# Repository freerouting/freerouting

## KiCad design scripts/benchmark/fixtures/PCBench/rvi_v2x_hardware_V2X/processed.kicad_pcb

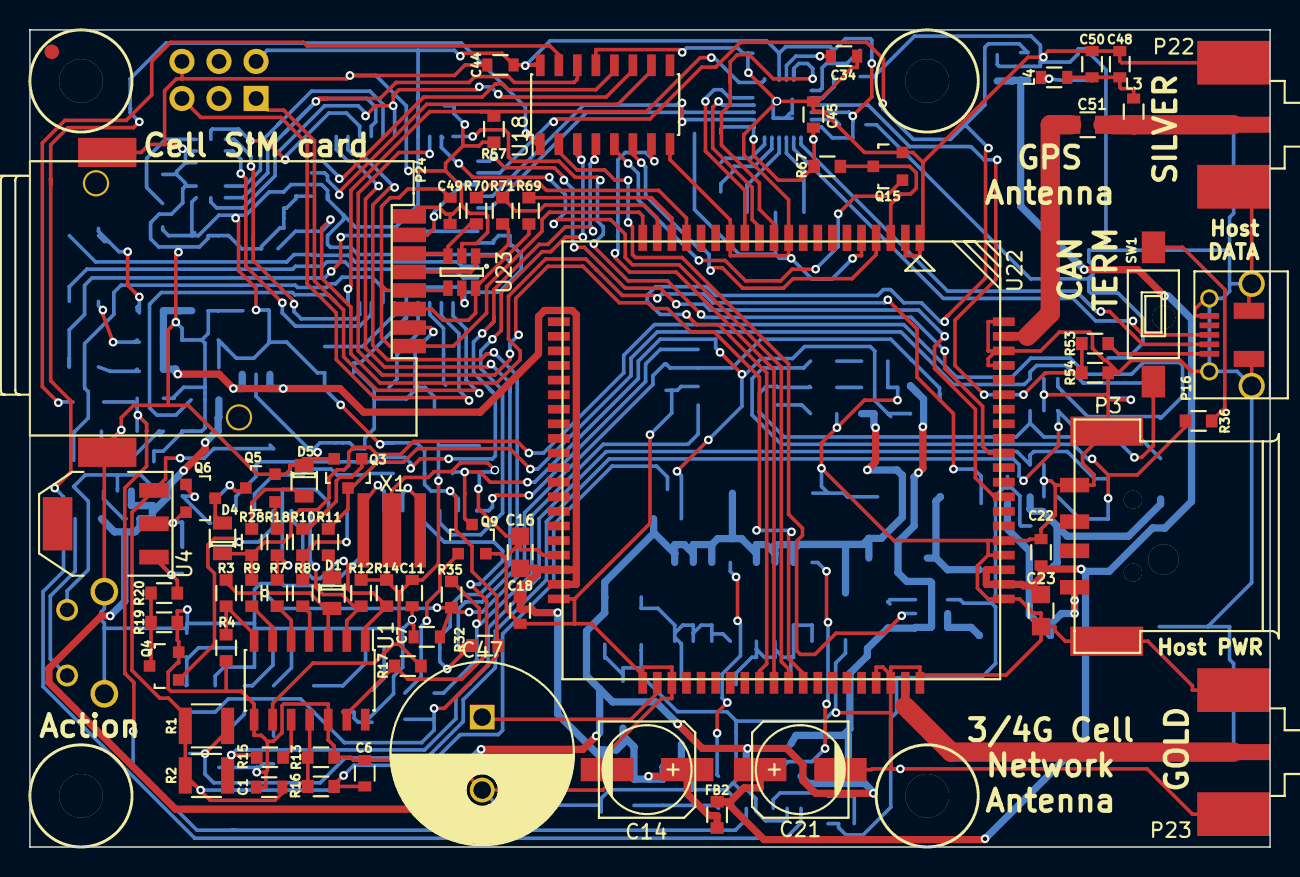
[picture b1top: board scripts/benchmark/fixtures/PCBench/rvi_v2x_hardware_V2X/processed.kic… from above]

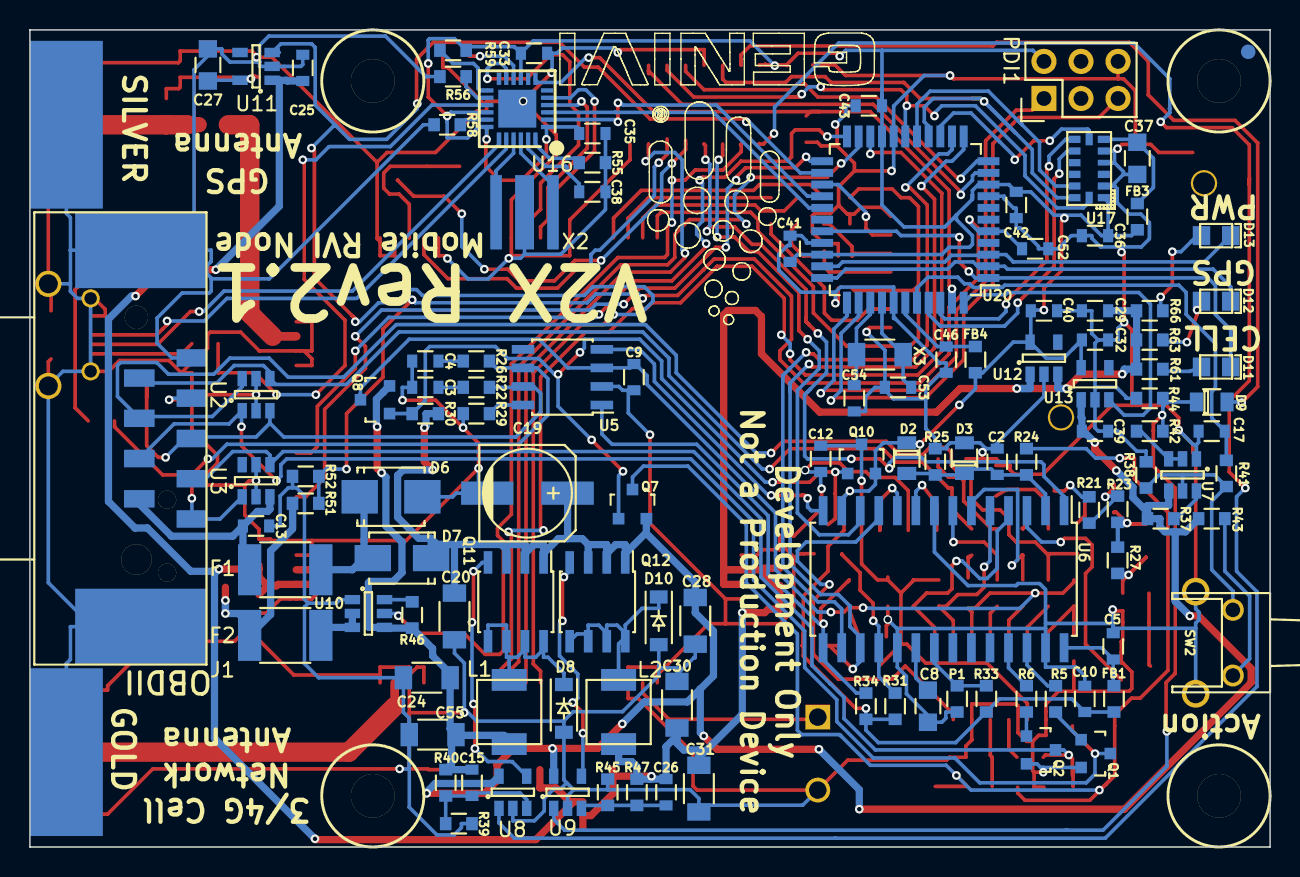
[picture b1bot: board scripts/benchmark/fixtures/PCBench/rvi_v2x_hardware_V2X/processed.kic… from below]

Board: 2 copper layers, 85.0 x 56.0 mm, 192 parts (115 on the bottom side), 142 nets.

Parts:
C1, C2, C6, C7, C12, C18, C25, C29, C32, C33, C36, C38, C39, C40, C41, C42, C43, C44, C45, C49, C52: 100N; C_0603_SM
C3, C4: 560P; C_0603_SM
C5, C9, C10, C11, C34, C35, C46: 1U; C_0603_SM
C8, C16, C23, C27, C37: 4U7; C_0805_SM
C13, C17, C22: 10N; C_0603_SM
C14, C21: 220U; c_elec_6.3x5.8
C15: 220P; C_0603_SM
C19: 100U; c_elec_6.3x5.8
C20, C28: 4U7; C_1206_SM
C24, C30, C31, C55: 10U; C_1206_SM
C26: 330P; C_0603_SM
C47: 0.1F; C_Radial_D12.5_L25_P5
C48: 56P; C_0603_SM
C50: 470P; C_0603_SM
C51: 150p; C_0805_SM
C53, C54: 9p; C_0603_SM
D1, D2, D3, D4, D5, D9: 4148; Diode_0805_12_SM
D6: SMBJ16A; SMB_Standard
D7: B320A-13-F; SMA_Standard
D8, D10: SBR3U30P1-7; SOD-123
D11: GREEN; 0805_LED
D12: BLUE; 0805_LED
D13: RED; 0805_LED
F1: 1.25A; R_1812
F2: 2A; R_1812
FB1, FB2, FB3, FB4: 220; R_0603_sm
J1: DB9; DB-9_SMT
L1, L2: 5U6; L_4.5x4.5
L3: 120N; L_0603_SM
L4: 330N; L_0603_SM
P1: NVM_RST; R_0603_sm
P3: USB_A; USB-A-SMT
P4: Board Mount 1; MountingHole_3mm
P5: Board Mount 2; MountingHole_3mm
P6: Board Mount 3; MountingHole_3mm
P7: Board Mount 4; MountingHole_3mm
P9: Ficudial2; Fiducial_1mm_Dia_2.54mm_Outer_CopperTop
P13: Ficudial2; Fiducial_1mm_Dia_2.54mm_Outer_CopperBottom
P16: USB_u; USB_Micro-B-DX4R005JJ2R1800
P22, P23: SMA; SMA-RA_142-0701-801
P24: SIM_SKT; 47553-1001
PDI1: AVR-PDI-6; Pin_Header_Straight_2x03
Q1, Q2, Q3, Q5: 2N3904; SOT_23_123
Q4, Q9, Q15: 2N7000; SOT_23_123
Q6: 3906; SOT_23_123
Q7, Q8, Q10: BSS84; SOT_23_123
Q11, Q12: IRF9335; SOIC-8_MOS
R1, R2: 510; R_1210_SM
R3, R21: 2K2; R_0603_sm
R4: 8.87K; R_0603_sm
R5, R6, R10, R32, R35: 1K; R_0603_sm
R7, R8, R9, R11, R12, R13, R14, R15, R16, R17, R18, R23, R25, R28, R30, R31, R37, R41, R46, R67: 10K; R_0603_sm
R19: 374; R_0603_sm
R20: 866; R_0603_sm
R22, R26, R36: 120; R_0603_sm
R24: 62K; R_0603_sm
R27: 240; R_0603_sm
R29: 4.7K; R_0603_sm
R33, R34: 100K; R_0603_sm
R38, R44: 24K; R_0603_sm
R39, R45: 2K0; R_0603_sm
R40: 10K5; R_0603_sm
R42, R43, R51, R52, R53, R54, R56, R57, R58, R59: 47K; R_0603_sm
R47: 8K2; R_0603_sm
R55: 12K; R_0603_sm
R61, R66: 330; R_0603_sm
R63: 220; R_0603_sm
R69, R70, R71: 22; R_0603_sm
SW1: SPST; SW_SPST_FSMSM_SM
SW2: SW_PUSH; PTS645VK58-2-LFS
U1: LM339; SOIC-14_3.9x8.7mm_Pitch1.27mm
U2, U3: ESDAxxSC6; SOT-23-6
U4: LM317; SOT-223
U5: MCP2551; SOIC-8_3.9x4.9mm_Pitch1.27mm
U6: STN1110; SOIC-28_7.5x17.9mm_Pitch1.27mm
U7, U10: FDC6326L; SOT-23-6
U8, U9: XRP6124; SOT-23-5
U11, U12, U13: TLV70012DCK; SOT-23-5
U16: USB2422; QFN-24-USB2422
U17: ADXL345; LGA-14_5x3mm
U18: 74HC595; SOIC-16_3.9x9.9mm_Pitch1.27mm
U20: ATXMEGA128A4U-AU; TQFP-44_10x10mm_Pitch0.8mm
U22: SIM5320
U23: MMQA5V6T3G; SOT-23-6
X1: 16MHz; AWSCR
X2: 24MHz; AWSCR
X3: 32.768K; C_1206_SM

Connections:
3V3: C10.1, C32.1, C33.1, C35.1, C36.1, C40.1, C41.1, C42.1, C43.1, C44.1, C45.1, D2.1, FB1.1, FB3.1, FB4.1, PDI1.2, Q10.2, R31.1, R32.1, R33.1, R34.1, R59.2, R67.2, U6.13, U12.5, U13.5, U16.1, U16.9, U16.16, U16.18, U17.1, U18.16, U20.9, U20.19, U20.31
3V3F1: C27.1, L4.1, U11.5
3V3_EN: U13.3, U20.44
3V3_F: C46.1, FB4.2, U20.39
4V1: C14.1, C16.1, C18.1, C26.1, C29.1, C30.1, C31.1, FB2.2, L2.2, R47.1, R61.2, R63.2, R66.2, U12.1, U12.3, U22.38, U22.39
4V1F1: C21.1, C22.1, C23.1, C25.1, FB2.1, U11.1, U22.62, U22.63
4V1_EN: D9.2, U18.15
5V0_A: C15.1, C24.1, C55.1, L1.2, Q8.2, R40.2, R46.1, U10.4
5V0_B: F2.1, U10.2, U10.3
5V0_B_EN: U10.5, U18.2
5V0_B_OUT: F2.2, P3.1, R51.2
5V0_EN: U8.1, U18.1
5V0_HOST: P16.1, R53.1
12V0_A: C13.1, F1.1, J1.9, U3.3
12V0_B: C19.1, C20.1, C28.1, C39.1, D7.1, Q7.2, Q11.2, Q12.2, R30.1, R37.2, R43.1, U7.4, U8.5, U9.5, U13.1
ACL_INT1: U17.8, U20.42
ACL_INT2: U17.9, U20.41
BAT_SAMPLE: C2.1, D2.2, D3.1, R24.2, R25.1, U6.2
BUTTON: C17.1, R41.2, U20.40
CAN_3.3V_SW: C11.1, C12.1, Q10.3, R12.1, R14.1, R17.1, U1.9
CAN_5V_SW: C7.1, C9.1, D1.2, Q8.3, R3.1, R35.1, U1.3, U5.3
CAN_12V_SW: C1.1, C6.1, Q7.3, R1.2, R2.2, R16.1, R24.1, U4.3
CAN_CLK: U6.9, X1.1
CAN_CLKN: U6.10, X1.2
CAN_H: J1.3, R22.1, SW1.1, U2.3, U5.7
CAN_L: J1.5, R26.1, R36.1, U3.1, U5.6
CAN_POWERDOWN: Q9.1, R31.2, U6.18
CAN_RX: U5.4, U6.14
CAN_RXD: U6.16, U20.13
CAN_TX: R34.2, R35.2, U5.1, U6.15
CAN_TXD: R32.2, U6.17, U20.12
GND: C1.2, C2.2, C3.2, C4.2, C5.2, C6.2, C7.2, C8.2, C9.2, C10.2, C11.2, C12.2, C13.2, C14.2, C16.2, C17.2, C18.2, C19.2, C20.2, C21.2, C22.2, C23.2, C24.2, C25.2, C27.2, C28.2, C29.2, C30.2, C31.2, C32.2, C33.2, C34.2, C35.2, C36.2, C37.2, C38.2, C39.2, C40.2, C41.2, C42.2, C43.2, C44.2, C45.2, C46.2, C47.2, C48.2, C49.2, C50.2, C52.2, C53.1, C54.1, C55.2, D3.2, D5.1, D6.2, D8.2, D10.2, J1.1, J1.2, J1.M, P1.2, P3.4, P3.5, P16.5, P16.6, P22.2, P23.2, P24.A, P24.B, P24.C5, P24.SW2, PDI1.6, Q1.2, Q2.2, Q3.2, Q4.2, Q5.2, Q9.2, Q15.2, R4.1, R13.2, R19.1, R25.2, R29.2, R38.1, R39.1, R44.1, R45.1, R52.1, R54.2, R55.1, R56.2, R57.2, R58.1, SW2.S, U1.8, U1.12, U2.2, U2.5, U3.2, U3.5, U5.2, U6.8, U6.19, U6.27, U7.1, U8.2, U9.2, U10.1, U11.2, U12.2, U13.2, U16.25, U17.2, U17.4, U17.5, U18.8, U18.13, U20.8, U20.18, U20.30, U20.38, U22.1, U22.2, U22.5, U22.10, U22.14, U22.37, U22.40, U22.41, U22.43, U22.57, U22.58, U22.60, U22.61, U22.64, U22.65, U22.77, U22.78, U22.80, U23.2, U23.5, X1.3, X2.3
GPS: C51.1, L3.1, P22.1
GPS_ANT: C51.2, U22.79
GPS_EN: U11.3, U20.24, U22.49
GSM_ANT: P23.1, U22.59
HOST_SC: C52.1, R51.1, R52.2, U20.5
HUB_CLK: U16.22, X2.2
HUB_CLKN: U16.21, X2.1
HUB_DM: P16.2, U16.19
HUB_DP: P16.3, U16.20
HUB_PWR_PRT1: R57.1, U16.7, U20.43
HUB_PWR_PRT2: U16.11, U22.11
HUB_SCL: R56.1, U16.14
HUB_SDA: R59.1, U16.13
HUB_SUSP_IND: R58.2, U16.17
ISO_K_TX: R6.1, U6.25
ISO_L_TX: R5.1, U6.26
ISO_RX: R17.2, U1.13, U6.11
J1850+: D4.1, J1.7, R9.2, R28.1, U2.6
J1850-: J1.6, Q3.3, R11.2, U2.4
J1850_BUS_+_TX: R7.2, R18.2, U6.6
J1850_BUS_-_TX: R8.2, R10.2, U6.7
K-LINE: J1.4, Q2.3, R2.1, R15.2, U3.4
L-LINE: J1.8, Q1.3, R1.1, U2.1
unnamed: C3.1, R22.2
unnamed: C4.1, R26.2
unnamed: C5.1, FB1.2, U6.28
unnamed: C8.1, U6.20
unnamed: C15.2, R39.2, R40.1, U8.3
unnamed: C26.2, R45.2, R47.2, U9.3
unnamed: C34.1, U16.10
unnamed: C37.1, FB3.2, U17.6
unnamed: C38.1, U16.23
unnamed: C47.1, U22.42
unnamed: C48.1, C50.1, L3.2, L4.2
unnamed: C53.2, U20.37, X3.1
unnamed: C54.2, U20.36, X3.2
unnamed: D1.1, R11.1
unnamed: D4.2, Q6.3
unnamed: D5.2, R28.2
unnamed: D6.1, D7.2, F1.2
unnamed: D8.1, L1.1, Q11.3
unnamed: D9.1, R42.1, R44.2, U9.1
unnamed: D10.1, L2.1, Q12.3
unnamed: D11.2, R61.1
unnamed: D12.2, R63.1
unnamed: D13.2, R66.1
unnamed: P1.1, R33.2, U6.21
unnamed: Q1.1, R5.2
unnamed: Q2.1, R6.2
unnamed: Q3.1, R10.1
unnamed: Q4.3, R19.2, R20.2
unnamed: Q5.1, R18.1
unnamed: Q5.3, R21.2
unnamed: Q6.1, R21.1, R23.2
unnamed: Q6.2, R23.1, R27.1, U4.2
unnamed: Q7.1, Q8.1, Q9.3, Q10.1, R30.2
unnamed: Q11.1, U8.4
unnamed: Q12.1, U9.4
unnamed: R3.2, R4.2, U1.7
unnamed: R7.1, U1.5
unnamed: R8.1, U1.4
unnamed: R9.1, U1.6
unnamed: R13.1, R16.2, U1.11
unnamed: R15.1, U1.10
unnamed: R20.1, R27.2, U4.1
unnamed: R29.1, U5.8
unnamed: R36.2, SW1.2
unnamed: R37.1, U7.6
unnamed: R38.2, R41.1, SW2.1, U7.5
unnamed: R42.2, U7.2, U7.3
unnamed: R43.2, SW2.2
unnamed: R46.2, U10.6
unnamed: R55.2, U16.24
unnamed: R69.1, U22.18
unnamed: R70.1, U22.17
unnamed: R71.1, U22.19
PDI: PDI1.1, U20.34
PWM/~VPW: Q4.1, U6.3
PWM_RX: R12.2, U1.2, U6.5
SEQ_DM: U16.2, U20.26
SEQ_DP: U16.3, U20.27
SEQ_LED1: D11.1, U20.1, U20.29
SEQ_LED2: D12.1, U20.2, U20.33
SEQ_LED3: D13.1, U20.3, U20.32
SEQ_MISO: U17.12, U20.16
SEQ_MOSI: U17.13, U18.14, U20.15
SEQ_RESET: PDI1.5, U20.35
SEQ_SCK: U17.14, U18.11, U20.17
SEQ_SS: U17.7, U20.14
SEQ_WAKE: U20.20, U22.52
SIMCARD: P24.SW1, U20.25
SIMCARD_CLK: P24.C3, R71.2, U23.1
SIMCARD_DATA: P24.C7, R70.2, U23.3
SIMCARD_RESET: P24.C2, R69.2, U23.6
SIMCARD_V: C49.1, P24.C1, P24.C6, U22.20, U23.4
SIM_DM: U16.4, U22.12
SIM_DP: U16.5, U22.13
SIM_NET: U20.21, U22.51
SIM_PWR_ON: Q15.1, U18.5
SIM_RESET: U18.6, U22.4
SIM_RXD: U20.23, U22.68
SIM_TXD: U20.22, U22.71
SIM_WAKE: U18.7, U22.50
SR_CLEAR: U18.10, U20.10
SR_LATCH: U18.12, U20.11
~CAN_RESET: U6.1, U18.4
~CAN_SLEEP: U6.12, U18.3
~HUB_RESET: R53.2, R54.1, U16.15
~SIM_PWR_ON: Q15.3, R67.1, U22.3
~VPW_RX: R14.2, U1.1, U6.4

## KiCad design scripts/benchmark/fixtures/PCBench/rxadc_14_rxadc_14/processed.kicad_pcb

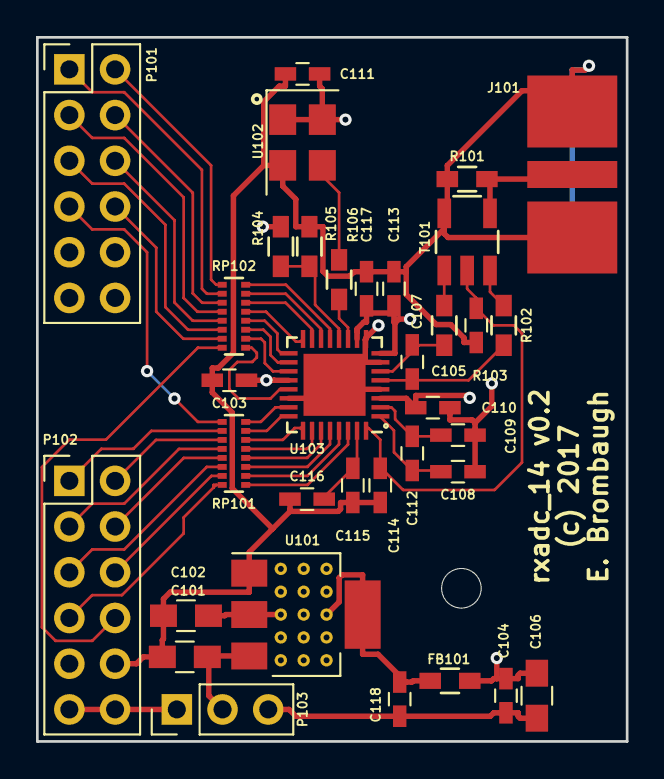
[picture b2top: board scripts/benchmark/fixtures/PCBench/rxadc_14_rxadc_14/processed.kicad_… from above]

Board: 4 copper layers, 32.8 x 39.1 mm, 35 parts (0 on the bottom side), 49 nets.

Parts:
C101, C102, C106: 10uf; C_0805_HandSoldering
C103, C104, C105, C108, C109, C110, C111, C113, C114, C115, C117, C118: 0.1uf; C_0603_HandSoldering
C107: 18pf; C_0603_HandSoldering
C112, C116: 1uf; C_0603_HandSoldering
FB101: FILTER; R_0603_HandSoldering
J101: SMA; SMA_END
P101, P102: CONN_02X06; Pin_Header_Straight_2x06_Pitch2.54mm
P103: CONN_01X03; Pin_Header_Straight_1x03_Pitch2.54mm
R101, R106: 50; R_0603_HandSoldering
R102, R103: 20; R_0603_HandSoldering
R104: 4k7; R_0603_HandSoldering
R105: 10k; R_0603_HandSoldering
RP101, RP102: 100; R_Array_EXB2HV
T101: TRANSFO4; Pulse_SMD_Balun
U101: LD1117S33CTR; SOT-223
U102: ASFL1-80.000MHZ-EC-T; Crystal_SMD_Abracon_ASFL1-4pin_5.0x3.2mm
U103: ADC14C105; QFN-32-1EP_5x5mm_Pitch0.5mm_extended_pad

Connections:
+3.3VADC: C104.1, C106.1, C110.1, C113.1, C117.1, FB101.2, R104.1, U103.3, U103.8, U103.10
+3V3: C102.1, C103.1, C111.1, C118.2, FB101.1, U101.2, U101.4, U102.1, U102.4, U103.20
+5V: C101.1, P103.2, U101.3
GND: C101.2, C102.2, C103.2, C104.2, C105.1, C106.2, C108.1, C109.1, C110.2, C111.2, C113.2, C114.1, C115.1, C116.1, C117.2, C118.1, J101.2, P101.9, P101.10, P102.9, P102.10, P103.3, R101.1, R105.2, T101.5, U101.1, U102.2, U103.4, U103.7, U103.9, U103.22, U103.33
unnamed: C105.2, C114.2, T101.2, U103.32
unnamed: C107.1, R102.2, U103.5
unnamed: C107.2, R103.2, U103.6
unnamed: C108.2, C112.1, U103.1
unnamed: C109.2, C112.2, U103.2
unnamed: C115.2, C116.2, U103.31
unnamed: J101.1, R101.2, T101.4
unnamed: P101.1, RP102.10
unnamed: P101.2, RP102.9
unnamed: P101.3, RP102.12
unnamed: P101.4, RP102.11
unnamed: P101.5, RP102.14
unnamed: P101.6, RP102.13
unnamed: P101.7, RP101.9
unnamed: P101.8, RP102.15
unnamed: P102.1, RP101.10
unnamed: P102.2, RP101.11
unnamed: P102.3, RP101.12
unnamed: P102.4, RP101.13
unnamed: P102.5, RP101.14
unnamed: P102.6, RP101.15
unnamed: P102.7, RP101.16
unnamed: P102.8, RP102.16
unnamed: P102.11, P102.12, P103.1
unnamed: R102.1, T101.3
unnamed: R103.1, T101.1
unnamed: R104.2, R105.1, U103.12
unnamed: R106.1, U103.11
unnamed: R106.2, U102.3
unnamed: RP101.1, U103.30
unnamed: RP101.2, U103.29
unnamed: RP101.3, U103.28
unnamed: RP101.4, U103.27
unnamed: RP101.5, U103.26
unnamed: RP101.6, U103.25
unnamed: RP101.7, U103.24
unnamed: RP101.8, U103.23
unnamed: RP102.1, U103.21
unnamed: RP102.2, U103.19
unnamed: RP102.3, U103.18
unnamed: RP102.4, U103.17
unnamed: RP102.5, U103.16
unnamed: RP102.6, U103.15
unnamed: RP102.7, U103.14
unnamed: RP102.8, U103.13

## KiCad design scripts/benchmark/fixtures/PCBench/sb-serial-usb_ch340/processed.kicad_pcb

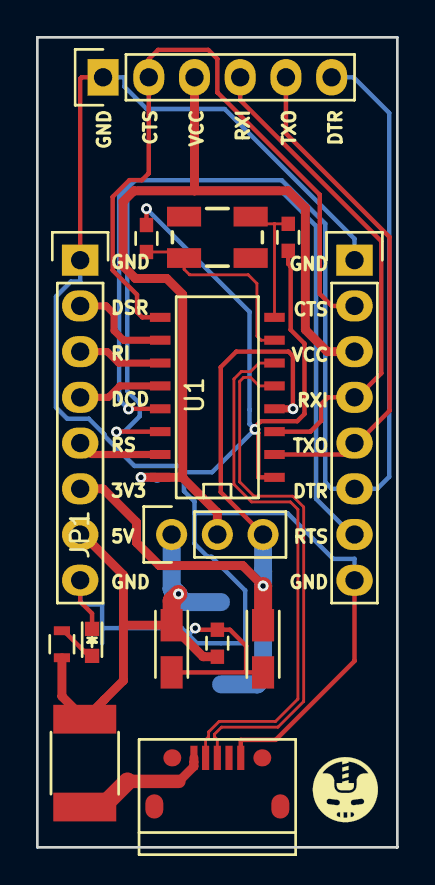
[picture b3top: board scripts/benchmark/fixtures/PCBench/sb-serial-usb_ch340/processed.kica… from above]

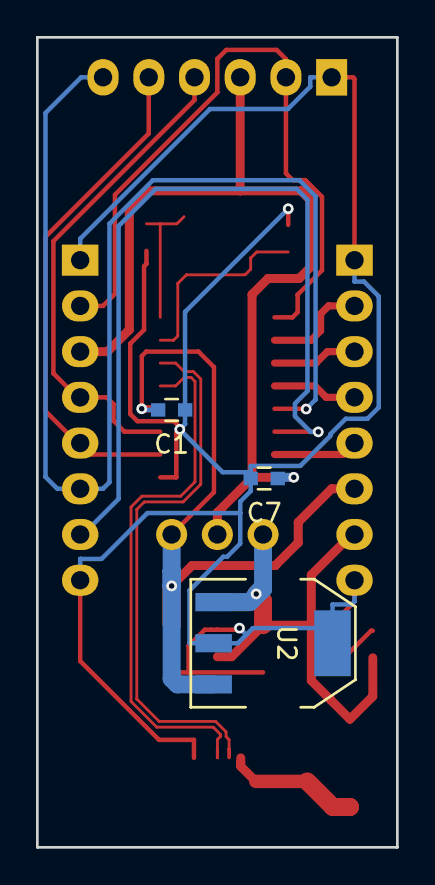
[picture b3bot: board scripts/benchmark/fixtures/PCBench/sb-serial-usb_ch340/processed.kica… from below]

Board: 2 copper layers, 20.0 x 45.0 mm, 18 parts (3 on the bottom side), 19 nets.

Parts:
C1: 10n; C_0603
C2, C3: 22p; C_0603
C4, C6: 10u 6V TANT; TantalC_SizeA_EIA-3216_Reflow
C5: 1u; C_0603
C7: 100n; C_0603
D1: BLUE; LED_0603
F1: 1.5A; R_1812
JP1: JUMPER3; Pin_Header_Straight_1x03
P1: CONN_01X06; Pin_Header_Straight_1x06
P2, P3: CONN_01X08; Pin_Header_Straight_1x08
P4: MINI-USB; USB_Micro-B
R1: 1K; R_0603
U1: CH340G; SO-16-N
U2: LDO MIC39100 3.3V; SOT-223
Y1: 12Mhz; CRYSTAL-SMD-5X3

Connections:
+5V: C4.1, C5.1, F1.2, JP1.1, P3.7, R1.2, U2.1
CTS: P1.2, P2.2, U1.9
D+: P4.3, U1.5
D-: P4.2, U1.6
DCD: P3.4, U1.12
DSR: P3.2, U1.10
DTR: P1.6, P2.6, U1.13
GND: C1.1, C2.2, C3.2, C4.2, C5.2, C6.2, C7.2, D1.1, P1.1, P2.1, P2.8, P3.1, P3.8, P4.5, U1.1, U2.2, U2.4
unnamed: C2.1, U1.7, Y1.1
unnamed: C3.1, U1.8, Y1.2
unnamed: D1.2, R1.1
unnamed: F1.1, P4.1
RI: P3.3, U1.11
RS232: P3.5, U1.15
RTS: P2.7, U1.14
RXI: P1.4, P2.4, U1.3
TXO: P1.5, P2.5, U1.2
V3: C1.2, C6.1, JP1.3, P3.6, U1.4, U2.3
VCC: C7.1, JP1.2, P1.3, P2.3, U1.16

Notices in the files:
scripts/benchmark/fixtures/PCBench/rxadc_14_rxadc_14/processed.kicad_pcb:
(c) 2017
